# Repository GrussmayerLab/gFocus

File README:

# Good Focus (gFocus)

**gFocus** is an active focus-lock system designed to maintain sharp focus during extended imaging experiments, such as single-molecule and live-cell imaging. It corrects axial drift (movement along the Z-axis) that can occur over time, ensuring your sample stays perfectly in focus.

This project is inspired by similar systems like qgFocus and pgFocus and follows the same naming convention.

## Key Features

- Real-time focus correction  
- Micro-Manager compatible  
- Flexible hardware support: works with any motorized Z-stage controllable through Micro-Manager  

## How It Works

1. An infrared laser beam is aimed slightly off-center into the objective lens.  
2. The beam reflects off the coverslip (glass slide) at the bottom of the sample.  
3. When the sample moves up or down (axial drift), the reflected beam shifts sideways.  
4. A light-array sensor detects this lateral shift by measuring the intensity profile of the reflected beam.  
5. The system calculates the amount of drift using a Gaussian fit to find the center of the beam.  
6. A feedback loop adjusts the Z-position of the stage to return the beam to its original position — restoring focus.  

## Getting Started

### Hardware Setup

1. In the `PCB` folder, you’ll find the **Gerber files** (for manufacturing the board), along with the **schematic** and **PCB design** in the `gFocus` folder. The project is designed using **KiCad**.  
2. A list of required components can be found in the **BOM (Bill of Materials)**.  
3. The mechanical design is available in the `enclosure` folder.

### Firmware Setup

1. gFocus uses the [XIAO SAMD21 microcontroller](https://nl.mouser.com/ProductDetail/Seeed-Studio/102010328?qs=GBLSl2AkirtQWO8CTzEK9g%3D%3D&srsltid=AfmBOoqHyFkl2Qpgyily5YNBzPaesjcrrXG1Ro79G8migozdgHgJccld).  
2. Follow this [getting started tutorial](https://wiki.seeedstudio.com/Seeeduino-XIAO/) to program the board using the `gFocus.ini` file.

### Software Setup

1. **Install Micro-Manager 2.0**  
   - Download and install the latest version of [Micro-Manager 2.0](https://download.micro-manager.org/nightly/2.0/Windows/).  
   - Copy the precompiled `EMU` folder (provided) into the root directory of Micro-Manager.

2. **Install the EMU Plugin** (for editing or customizing the interface)  
   - Follow the instructions here: [EMU Guide](https://jdeschamps.github.io/EMU-guide/)

3. **Install the gFocus Plugin**  
   - Copy the `gFocus.jar` file into the `EMU` folder in your Micro-Manager directory.

4. **Install the Device Adapter**  
   - Copy the `mmgr_dal_gFocus.dll` file into the root directory of Micro-Manager.  
   - To modify or rebuild the adapter:  
     - Follow the [Micro-Manager Visual Studio setup guide](https://micro-manager.org/Visual_Studio_project_settings_for_device_adapters)  
     - Place `.h` files in the **header** folder and `.cpp` files in the **source** folder.  
     - Compile the project and place the resulting `.dll` file into the Micro-Manager root directory.

## Usage

1. Connect the gFocus system to your PC using a USB-C cable.  
2. In Micro-Manager, go to **Device > Hardware Configuration Wizard** and add `gFocus` to your device list.  
3. Launch the plugin: **Plugins > User Interface > EMU** — the gFocus control panel will open.

You should see the following interface:

Next, go to the **Configuration** tab and enter the required properties:

Now you're ready to go!

In the interface:
- You can adjust the **exposure time** and **averaging** for the light-array sensor.
- Press the `Enable` button to monitor pixel data from the sensor.
- Use the `Calibrate` button to run a calibration script that determines the relationship between pixel position and Z-distance.
- Once calibration is complete, the `Lock` button becomes available, activating the focus lock.

**Happy Imaging!**

## License

This project is licensed under the MIT License. See the `LICENSE` file for details.

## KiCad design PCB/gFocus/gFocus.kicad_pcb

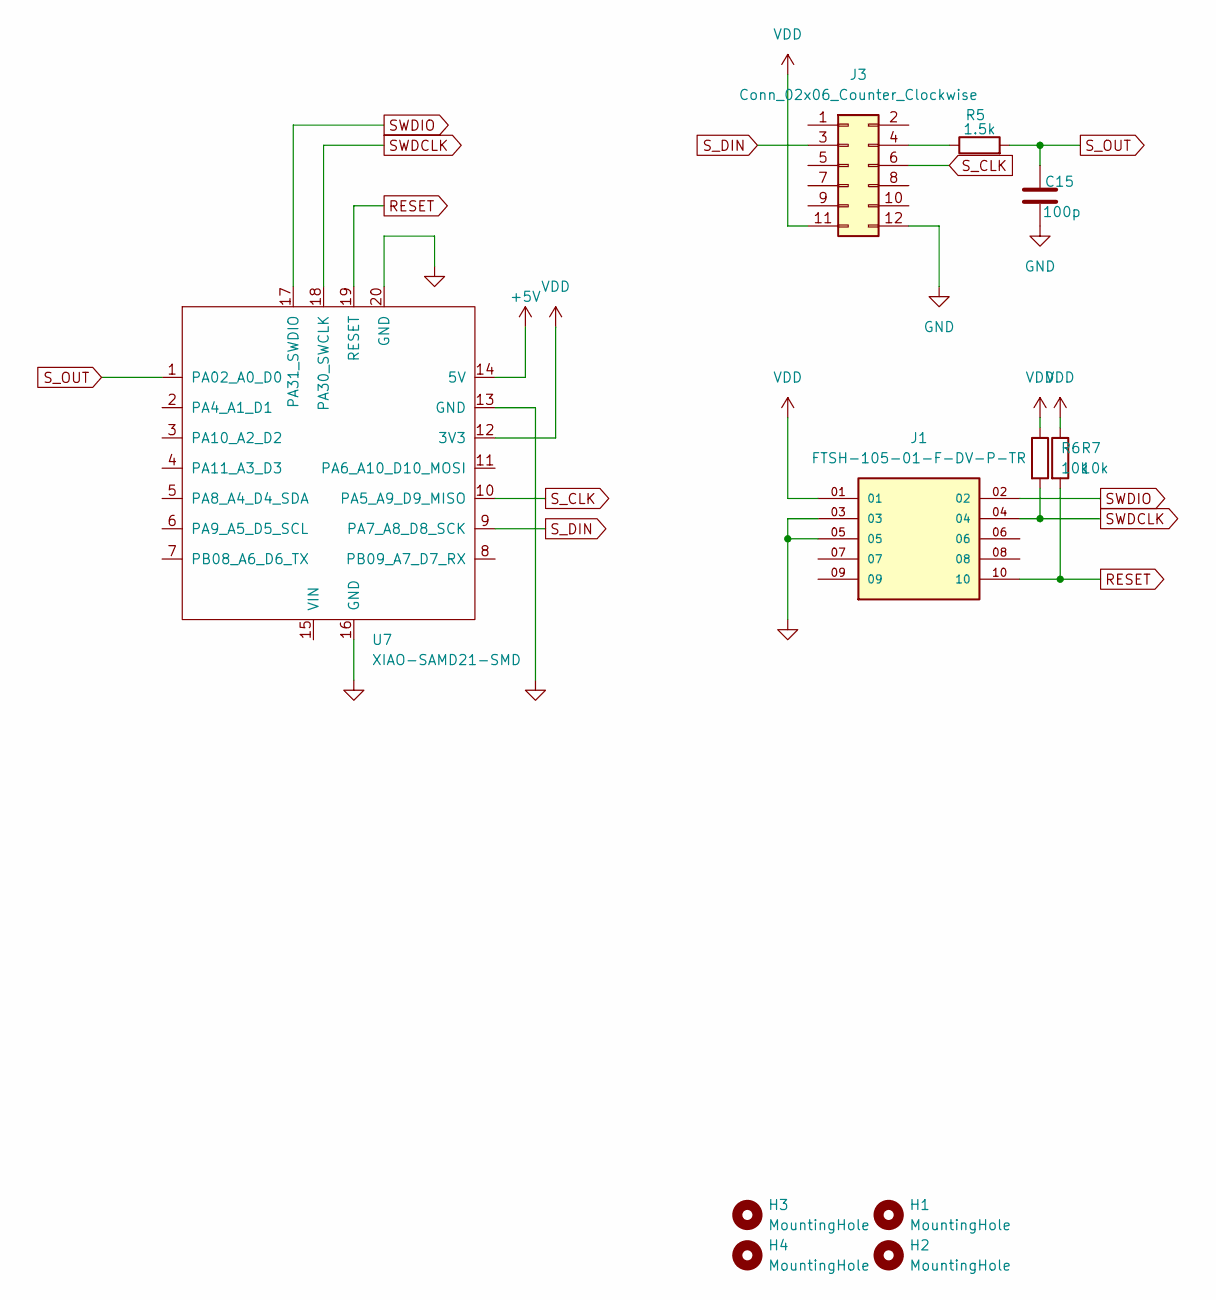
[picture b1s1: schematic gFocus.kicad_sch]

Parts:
C15: 100p; C_0805_2012Metric
H1, H2, H3, H4: MountingHole; MountingHole_3.2mm_M3
J1: FTSH-105-01-F-DV-P-TR; SAMTEC_FTSH-105-01-F-DV-P-TR; PARTREV R
J3: Conn_02x06_Counter_Clockwise; Hirose_DF11-12DP-2DSA_2x06_P2.00mm_Vertical
R5: 1.5k; R_0805_2012Metric
R6, R7: 10k; R_0805_2012Metric
U7: XIAO-SAMD21-SMD

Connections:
+5V: U7.14 (5V)
GND: C15.2, J1.03, J1.05, J3.12, U7.13 (GND), U7.16 (GND), U7.20 (GND)
unnamed: J3.4, R5.1
RESET: J1.10, R7.2, U7.19 (RESET)
SWDCLK: J1.04, R6.2, U7.18 (PA30_SWCLK)
SWDIO: J1.02, U7.17 (PA31_SWDIO)
S_CLK: J3.6, U7.10 (PA5_A9_D9_MISO)
S_DIN: J3.3, U7.9 (PA7_A8_D8_SCK)
S_OUT: C15.1, R5.2, U7.1 (PA02_A0_D0)
VDD: J1.01, J3.11, R6.1, R7.1, U7.12 (3V3)

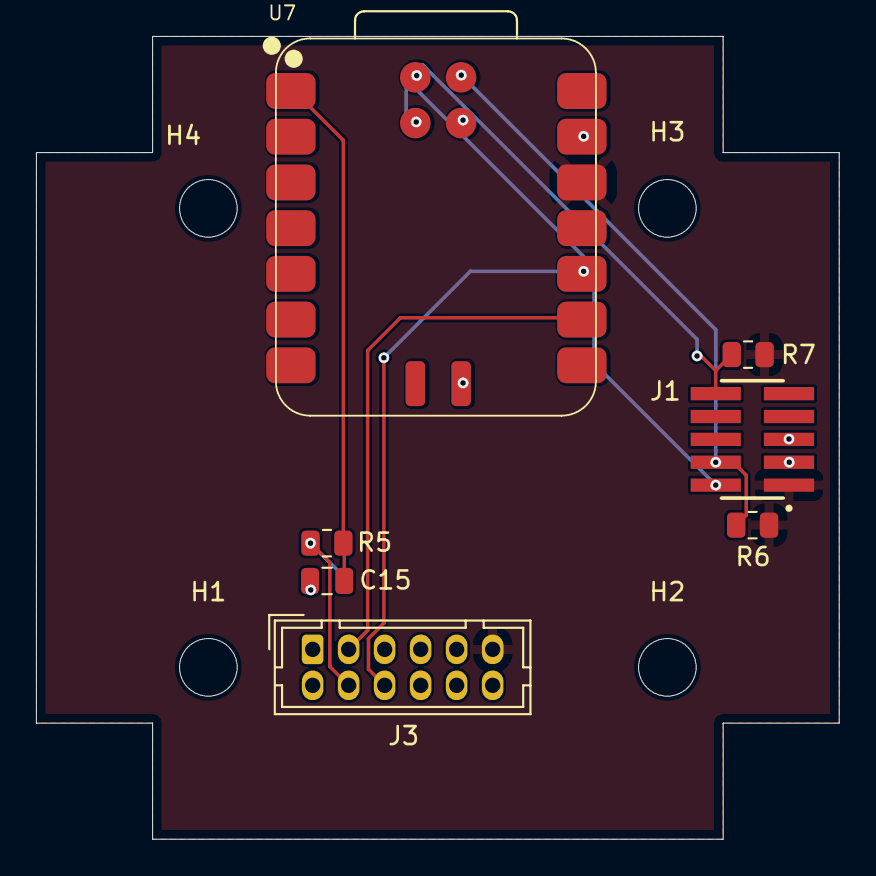
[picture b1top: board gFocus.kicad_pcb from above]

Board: 2 copper layers, 44.6 x 44.6 mm, 11 parts (0 on the bottom side), 9 nets.

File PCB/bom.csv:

U7,XIAO-SAMD21-SAMD21
R6,R7,10k,0805
R5,1.5k,0805
C15,100p,0805
J3,DF11-12DS-2DSA(06)
J1,FTSH-105-01-F-DV-P-TR

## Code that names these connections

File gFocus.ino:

#include <SPI.h>
#include <Arduino.h>

#define CMD_GET_DEVICE 0x01
#define CMD_SET_SETTINGS 0x2
#define CMD_GET_DATA 0x03

#define START_FLAG 0x7E
#define END_FLAG 0x7F
#define DEVICE_ID 0x01
#define RESPONSE_ERROR 0xFF
#define BUFFER_SIZE 64
#define QUEUE_SIZE 10 // Number of messages in FIFO

#define S_CLK 9
#define S_DIN 8
#define S_OUT A0

#define TIMER_INTERVAL_FQ 10  // 10 Hz

#define ACK 0xAA
#define NACK 0x55
#define MAX_RETRIES 3
#define ACK_TIMEOUT_MS 100

float exposureTime = 0.1f;  // 100 µs
uint16_t averagedData[128] = {0};
uint16_t tempBuffer[128];
uint8_t averageCount = 1;     // Average 1 run

// FIFO Queue for messages
typedef struct {
    uint8_t data[BUFFER_SIZE];
    int length;
} Message;

Message fifo_queue[QUEUE_SIZE];
int fifo_head = 0;
int fifo_tail = 0;

uint8_t Serial_buffer[BUFFER_SIZE];
int buffer_index = 0;

void checkAndExtractMessages();
void processSerialCommand();
uint8_t calculateCRC(uint8_t *args, int argCount);
void handleGetDevice();
void handleGetSettings(uint8_t average, float exposure);
void initializeLightSensor();
void onTimerInterrupt();
void runMeasurement(uint16_t* buffer);
void sendData(uint16_t* buffer, size_t length);
bool waitForAck(unsigned long timeout);
// FIFO Helper Functions
bool isFIFOFull() { return ((fifo_head + 1) % QUEUE_SIZE) == fifo_tail; }
bool isFIFOEmpty() { return fifo_head == fifo_tail; }

void ClockPulse() {
  delayMicroseconds(1);
  digitalWrite(S_CLK, HIGH);
  delayMicroseconds(1);
  digitalWrite(S_CLK, LOW);
}

void enqueueMessage(uint8_t *data, int length) {
    if (!isFIFOFull()) {
        memcpy(fifo_queue[fifo_head].data, data, length);
        fifo_queue[fifo_head].length = length;
        fifo_head = (fifo_head + 1) % QUEUE_SIZE;
    }
}

bool dequeueMessage(Message *msg) {
    if (!isFIFOEmpty()) {
        *msg = fifo_queue[fifo_tail];
        fifo_tail = (fifo_tail + 1) % QUEUE_SIZE;
        return true;
    }
    return false;
}

void setup() {
    digitalWrite(LED_BUILTIN, LOW);
    Serial.begin(115200);
    pinMode(S_CLK, OUTPUT);
    pinMode(S_DIN, OUTPUT);
    // analogReadResolution(12); // Set to 12 bits
    initializeLightSensor();
}

void loop() {
  // triggerCamera();
  // delay(1000);
    int ch = Serial.read();
    if (ch != -1) {
        Serial_buffer[buffer_index++] = (uint8_t)ch;

        if (buffer_index >= BUFFER_SIZE) {
            buffer_index = 0; // Prevent overflow
        }

        // Extract messages from buffer and store them in FIFO
        checkAndExtractMessages();
    }

    // Process the next available command in FIFO
    if (!isFIFOEmpty()) {
        processSerialCommand();
    }
}

void checkAndExtractMessages() {
    int startIdx = -1;
    int endIdx = -1;

    // Scan the buffer to find the first START_FLAG and END_FLAG
    for (int i = 0; i < buffer_index; i++) {
        if (Serial_buffer[i] == START_FLAG && startIdx == -1) {
            startIdx = i; // Mark the start of a valid message
        }
        if (Serial_buffer[i] == END_FLAG && startIdx != -1) {
            endIdx = i; // Found a complete message
            int messageLength = endIdx - startIdx + 1;

            // Store the valid message in FIFO
            enqueueMessage(&Serial_buffer[startIdx], messageLength);

            // Remove processed message from buffer
            memmove(Serial_buffer, &Serial_buffer[endIdx + 1], BUFFER_SIZE - (endIdx + 1));
            buffer_index -= (endIdx + 1);

            // Reset start/end markers and continue scanning
            startIdx = -1;
            endIdx = -1;
            i = -1; // Restart loop from beginning
        }
    }

    // If buffer is full but no complete message, reset to prevent overflow
    if (buffer_index >= BUFFER_SIZE) {
        buffer_index = 0;
        memset(Serial_buffer, 0, sizeof(Serial_buffer));
    }
}

void processSerialCommand() {
    Message msg;
    if (!dequeueMessage(&msg)) return;

    uint8_t command, length, receivedCRC, calculatedCRC;
    uint8_t channel_id;
    uint8_t average;
    float exposure;
    uint16_t value;

    if (msg.length < 4) return; // Ignore incomplete packets

    command = msg.data[1];
    length = msg.data[2];
    receivedCRC = msg.data[length];

    // Validate CRC
    calculatedCRC = calculateCRC(&msg.data[1], length - 1);
    if (calculatedCRC != receivedCRC) {
        Serial.write(RESPONSE_ERROR);
        return;
    }

    switch (command) {
        case CMD_GET_DEVICE:
            digitalWrite(LED_BUILTIN, HIGH);  // turn the LED on (HIGH is the voltage level)
            handleGetDevice();
            break;
        case CMD_SET_SETTINGS:
            if (length < 6) {
                Serial.write(RESPONSE_ERROR);
                return;
            }
            average = msg.data[3]; // uint8_t
            memcpy(&exposure, &msg.data[4], sizeof(float)); // Extract float from bytes
            exposureTime = exposure;
            averageCount = average;
            break;
        case CMD_GET_DATA:
            triggerCamera();
            break;
        default:
            Serial.write(RESPONSE_ERROR);
            break;
    }
}

uint8_t calculateCRC(uint8_t *args, int argCount) {
    uint8_t crc = 0;
    for (int i = 0; i < argCount; i++) {
        crc ^= args[i];
    }
    return crc;
}

void handleGetDevice() {
    uint8_t response[] = {CMD_GET_DEVICE, 0x01, DEVICE_ID};
    uint8_t crc = calculateCRC(response, 3);

    Serial.write(START_FLAG);
    for (int i = 0; i < 3; i++) {
        Serial.write(response[i]);
    }
    Serial.write(crc);
    Serial.write(END_FLAG);
}

void triggerCamera() {
  // Clear sum buffer if it's the first average cycle
  memset(averagedData, 0, sizeof(averagedData));

  for (int n = 0; n < averageCount; n++) {
    runMeasurement(tempBuffer);

    // Sum up results
    for (int i = 0; i < 128; i++) {
      averagedData[i] += tempBuffer[i];
    }
  }

  // Final average
  for (int i = 0; i < 128; i++) {
    averagedData[i] /= averageCount;
  }

  // Send data in four chunks of 32 values each
  for (int chunk = 0; chunk < 4; chunk++) {
    int start = chunk * 32;
    int retries = 0;
    bool success = false;

    while (retries < MAX_RETRIES) {
      sendData(&averagedData[start], 32);
      if (waitForAck(ACK_TIMEOUT_MS)) {
        success = true;
        break;
      } else {
        retries++;
      }
    }
  }
}

void runMeasurement(uint16_t* buffer) {
  digitalWrite(S_DIN, HIGH);
  ClockPulse();
  digitalWrite(S_DIN, LOW);

  unsigned int microSeconds = (unsigned int) exposureTime * 1000;
  delayMicroseconds(microSeconds);

  buffer[0] = analogRead(S_OUT);

  for (int i = 1; i < 128; i++) {
    ClockPulse();
    buffer[i] = analogRead(S_OUT);
  }
  ClockPulse();
  delayMicroseconds(20);
}

void sendData(uint16_t* buffer, size_t length) {
  // Total size: CMD (1) + LEN (1) + DATA (length) + CRC (1) + flags (2)
  size_t payloadSize = 1 + 1 + 1*length; 
  uint8_t response[payloadSize+3];

  // First packet: low bytes
  response[0] = CMD_GET_DATA;
  response[1] = length;

  for (size_t i = 0; i < length; i++) {
    response[2 + i] = buffer[i] & 0xFF;  // Low byte
  }


  uint8_t crc1 = calculateCRC(response, payloadSize);

  Serial.write(START_FLAG);
  Serial.write(response, payloadSize);
  Serial.write(crc1);
  Serial.write(END_FLAG);

  delayMicroseconds(1000);

  // Second packet: high bytes
  response[0] = CMD_GET_DATA;  // different command for clarity
  response[1] = length;
  
  for (size_t i = 0; i < length; i++) {
    response[2 + i] = (buffer[i] >> 8) & 0xFF;  // High byte
  }

  uint8_t crc2 = calculateCRC(response, payloadSize);

  Serial.write(START_FLAG);
  Serial.write(response, payloadSize);
  Serial.write(crc2);
  Serial.write(END_FLAG);
}

void initializeLightSensor() {
  // Clock out any excisting SI pulse through the CCD register
  for (int i = 0; i < 130; i++) {
    ClockPulse();
  }

  // Send an SI pulse and clock out the sensor register
  digitalWrite(S_DIN, HIGH);
  ClockPulse();
  digitalWrite(S_DIN, LOW);

  for (int i = 1; i < 128; i++) {
    ClockPulse();
  }
}

bool waitForAck(unsigned long timeout) {
  unsigned long startTime = millis();
  while (millis() - startTime < timeout) {
    if (Serial.available()) {
      int resp = Serial.read();
      if (resp == ACK) return true;
      if (resp == NACK) return false;
    }
  }
  return false;  // Timeout
}

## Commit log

2025-05-27 init
2025-06-02 added drivers
2025-06-03 Gaussian fit with least squares
2025-06-03 fixed least squares opt
2025-06-03 camera polling 5 times
2025-06-03 without sleep delay
2025-06-03 get name of focus stage
2025-06-03 CameraPollingTask added function snapOnce for calibration
2025-06-03 returning to home after calibration
2025-06-03 max retries to 10
2025-06-03 calibration step size 0.25um
2025-06-03 driver retries
2025-06-03 added flush after serial.write for driver
2025-06-03 mm driver without retries
2025-06-05 handshake protocol for sending camera data and cut up into 32 bytes
2025-06-13 implemented focus lock
2025-06-13 added README
2025-06-13 fix readme
2025-06-13 md complete
2025-06-17 XIAO board is added and fixed graph bugs
2025-06-24 private CMMCore for light sensor polling
2025-06-24 log private core init
2025-06-24 private core log message
2025-06-24 gFocus generic driver
2025-06-24 generic device in init module
2025-06-24 average to 1 and back to as camera devicee
2025-06-24 set average and exposure in private core
2025-06-24 fix set property camera
2025-06-24 camera polling task
2025-06-24 gaussian fit bug
2025-06-24 attach and detatch
2025-06-24 deleting polling task from monitoring
2025-06-24 debug property name
2025-06-24 property name equals bug
2025-06-24 test
2025-06-30 second MMCore
2025-06-30 faster polling
2025-07-01 added bom
2025-07-01 restart if crash
2025-07-01 dark mode
2025-07-01 updated readme and driver
2025-12-05 updated readme and files
2025-12-05 updated reamde
2025-12-05 readme assembly
2025-12-08 updated licenses
2025-12-08 updated bom of enclosure
2025-12-08 updated readme and bom with cost estimation
2025-12-08 added table in REAMDE
